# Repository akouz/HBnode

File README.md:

# HBnode
Microcontroller boards for [HBus](https://github.com/akouz/HBus) based on [AVR64DD32](https://www.microchip.com/en-us/product/avr64dd32). Form factor is the same as Arduino Pro Mini and Arduino Nano, while pinout made as close as possible. Firmware update made using on-board I2C EEPROM; custom bootloader occupies 1K bytes. 

[Programmer HEXloader.exe](https://github.com/akouz/HBnode/tree/main/AVR64DD32/Programmer/Software) can transfer compiled hex files from PC to EEPROM via Arduino UNO running [sketch HEXloader.ino](https://github.com/akouz/HBnode/tree/main/AVR64DD32/Programmer/Sketch). When a board used in HBus network, firmware can be updated remotely via HBus.

# How to program HBnode board:
1. Burn bootloader. 
   Plug PicKit4 to 4-pin connector, apply power to the board and burn [HBnode bootloader](https://github.com/akouz/HBnode/blob/main/AVR64DD32/Bootloader) using MPLAB.X IDE or MPLAB.X IPE.

2. Load HBus sketch.
   Connect HBnode to the [programmer](https://github.com/akouz/HBnode/tree/main/AVR64DD32/Programmer) and transfer selected sketch to the HBnode using [HEXLoader](https://github.com/akouz/HBnode/tree/main/AVR64DD32/Programmer/Software)
   
3. When a correct sketch is programmed to the HBnode, a new sketch can be loaded to the board via HBus using [NodeTest](https://github.com/akouz/HBus/tree/master/NodeTest)

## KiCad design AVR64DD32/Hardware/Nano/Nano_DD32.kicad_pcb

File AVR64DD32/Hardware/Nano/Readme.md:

Connector P4 for UPDI programmer/debugger. To program bootloader I used MPLAB X rev 6.05 and PicKit4.

Connector P3 for a I2C programmer or for external monitor based on FT200XD. [I2C programmer](https://github.com/akouz/HBnode/tree/main/AVR64DD32/Programmer) writes application code into serial EEPROM U1, after reset bootloader copies EEPROM into program memory. Arduino UNO can be used as [I2C programmer](https://github.com/akouz/HBnode/tree/main/AVR64DD32/Programmer).

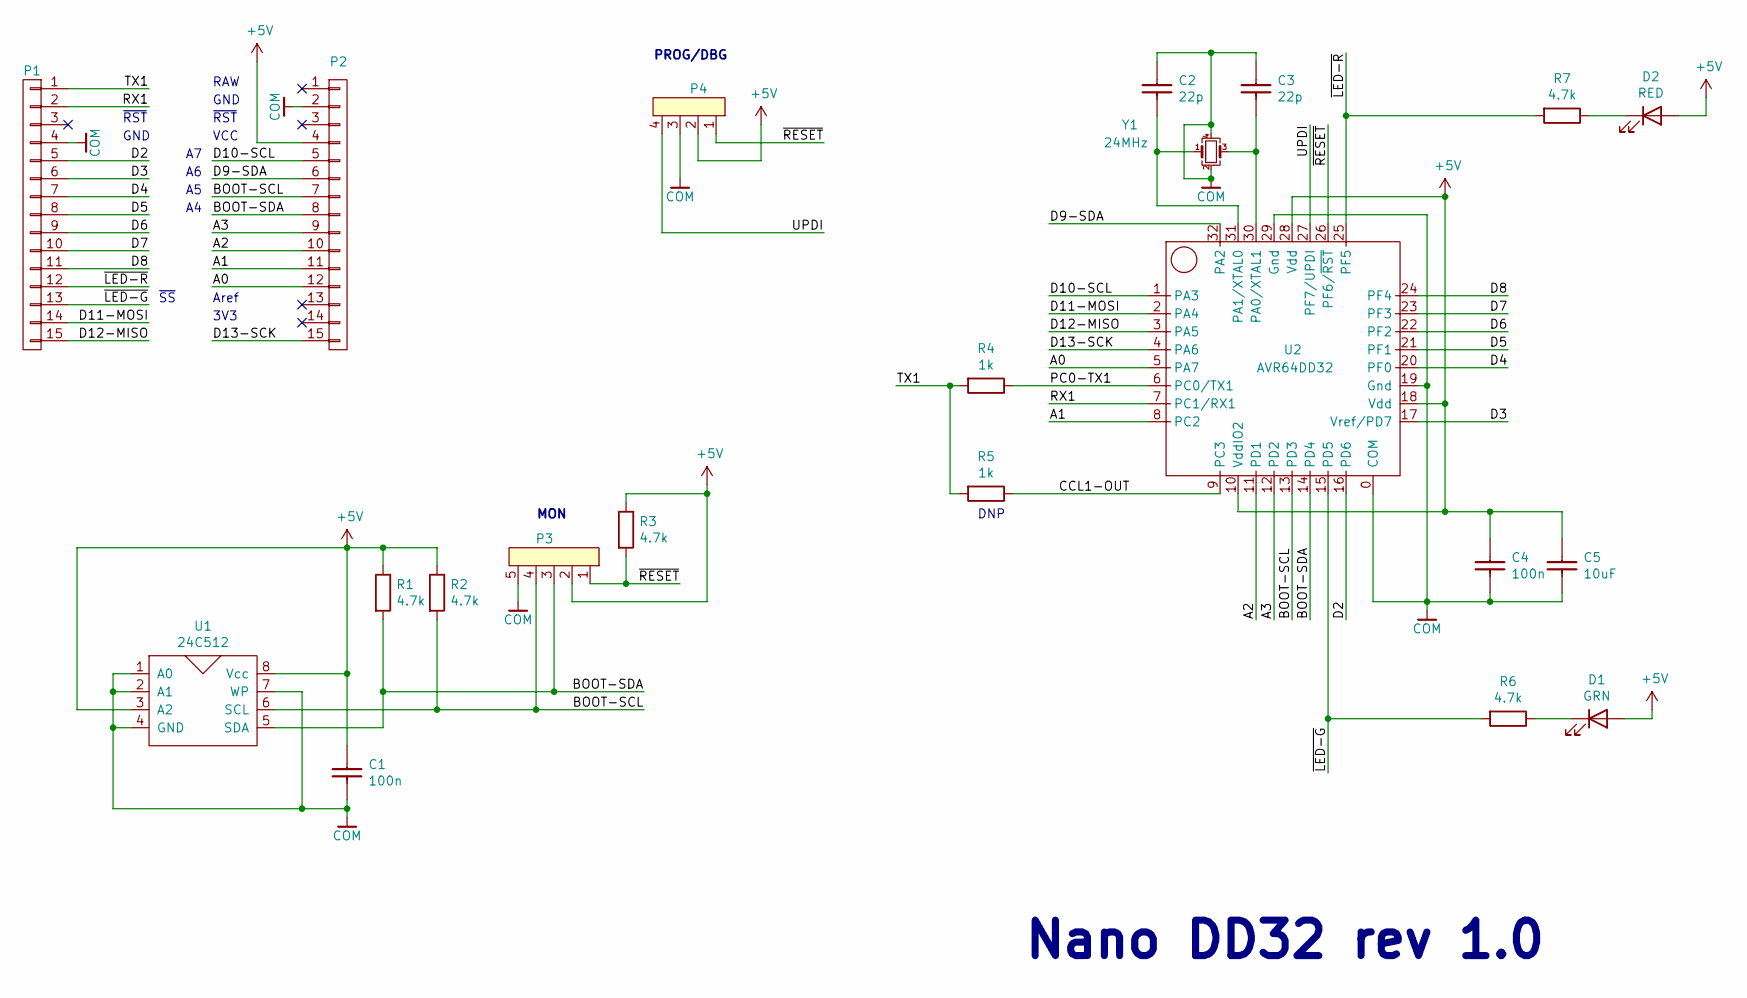
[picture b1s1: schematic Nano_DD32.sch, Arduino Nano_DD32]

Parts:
C1, C4: 100n; 0603
C2, C3: 22p; 0603
C5: 10uF; 0805
D1: GRN; 0603_LED
D2: RED; 0603_LED
P1, P2: CONN_01X15; PinHeader_1x15_P2.54mm_Vertical
P3: CONN_01X05
P4: CONN_01X04; PinHeader_1x04_P2.54mm_Vertical
R1, R2, R3, R6, R7: 4.7k; 0603
R4, R5: 1k; 0603
U1: 24C512; TSSOP-8_4.4x3mm_P0.65mm
U2: AVR64DD32; QFN-32-1EP_5x5mm_P0.5mm_EP3.1x3.1mm_pin0
Y1: 24MHz; Crystal_SMD_2520-4Pin_2.5x2.0mm

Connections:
+5V: C1.1, C4.1, C5.1, D1.2 (A), D2.2 (A), P2.4, P3.2, P4.2, R1.1, R2.1, R3.1, U1.3 (A2), U1.8 (Vcc), U2.10 (VddIO2), U2.18 (Vdd), U2.28 (Vdd)
/A0: P2.12, U2.5 (PA7)
/A1: P2.11, U2.8 (PC2)
/A2: P2.10, U2.11 (PD1)
/A3: P2.9, U2.12 (PD2)
/BOOT-SCL: P2.7, P3.4, R2.2, U1.6 (SCL), U2.13 (PD3)
/BOOT-SDA: P2.8, P3.3, R1.2, U1.5 (SDA), U2.14 (PD4)
/CCL1-OUT: R5.1, U2.9 (PC3)
/D2: P1.5, U2.16 (PD6)
/D3: P1.6, U2.17 (Vref/PD7)
/D4: P1.7, U2.20 (PF0)
/D5: P1.8, U2.21 (PF1)
/D6: P1.9, U2.22 (PF2)
/D7: P1.10, U2.23 (PF3)
/D8: P1.11, U2.24 (PF4)
/D9-SDA: P2.6, U2.32 (PA2)
/D10-SCL: P2.5, U2.1 (PA3)
/D11-MOSI: P1.14, U2.2 (PA4)
/D12-MISO: P1.15, U2.3 (PA5)
/D13-SCK: P2.15, U2.4 (PA6)
/PC0-TX1: R4.1, U2.6 (PC0/TX1)
/RX1: P1.2, U2.7 (PC1/RX1)
/TX1: P1.1, R4.2, R5.2
/UPDI: P4.4, U2.27 (PF7/UPDI)
/~LED-G: P1.13, R6.2, U2.15 (PD5)
/~LED-R: P1.12, R7.2, U2.25 (PF5)
/~RESET: P3.1, P4.1, R3.2, U2.26 (PF6/~RST)
COM: C1.2, C2.1, C3.1, C4.2, C5.2, P1.4, P2.2, P3.5, P4.3, U1.1 (A0), U1.2 (A1), U1.4 (GND), U1.7 (WP), U2.0 (COM), U2.19 (Gnd), U2.29 (Gnd), Y1.2, Y1.4
unnamed: C2.2, U2.31 (PA1/XTAL0), Y1.1
unnamed: C3.2, U2.30 (PA0/XTAL1), Y1.3
unnamed: D1.1 (K), R6.1
unnamed: D2.1 (K), R7.1

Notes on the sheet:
~RST
RAW
GND
VCC
PROG/DBG
MON
~SS
Nano DD32 rev 1.0
Aref
3V3
DNP

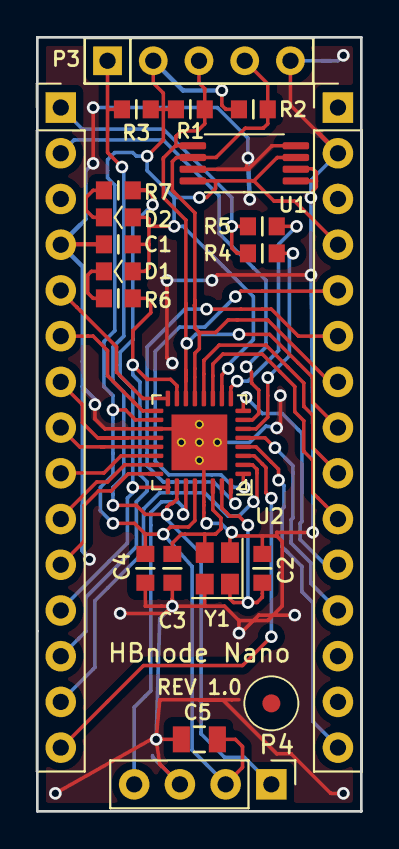
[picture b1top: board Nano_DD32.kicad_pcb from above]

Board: 2 copper layers, 18.0 x 43.0 mm, 22 parts (0 on the bottom side), 32 nets.

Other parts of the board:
FID1: FIDUCIAL; Fiducial

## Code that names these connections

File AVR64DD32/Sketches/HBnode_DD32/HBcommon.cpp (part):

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// =============================================
void EVSYS_config(void)
{
    EVSYS.CHANNEL2 = 0x4E;          // channel 2 source is PD6, it is connected to 
                                    // PC1 (USART1 RxD) by h/w link
    EVSYS.USERCCLLUT2A = 0x03;      // CCL LUT2 event A connected to channel 2
    //EVSYS.USEREVSYSEVOUTA = 0x03;   // EVSYS EVOUTA pin PA2 (D9) connected to channel 2, debug
}
// =============================================
// Configure CCL
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    CCL.LUT0CTRLB = 0x00;   
    CCL.LUT0CTRLC = 0x08;   // INSEL2 to USART1 TxD    
    CCL.TRUTH0    = 0xF0;      
    // CCL.LUT0CTRLA = 0x41;   // OUTEN to PA3,  debug 

    // -----------
    // LUT1 - combines D flip-flop output and USART1 TxD
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    CCL.LUT1CTRLB = 0x02;   // INSEL0 to LUT2 output, eg to D flip-flop output
    CCL.LUT1CTRLC = 0x08;   // INSEL2 to USART1 TxD   
    CCL.TRUTH1    = 0xFA;   // when D flip-flop is set then output is high, eg recessive state on HBus
    CCL.LUT1CTRLA = 0x61;   // OUTEN to PC3, filter, clock CLK_PER 

    // -----------
    // LUT2 - D input of flip-flop and flip-flop output
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
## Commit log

2023-04-25 Create AVR64DD32
2023-08-20 Add files via upload
    rev 1.8
2023-08-21 Add files via upload
    rev 1.9
2023-09-13 Add files via upload
    preliminary rev 0.9
2023-10-19 Add files via upload
    rev 1.1
2023-10-19 Add files via upload
    rev 0.14

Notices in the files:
AVR64DD32/Sketches/HBnode_DD32/HBcommon.cpp:
(c) 2023 Alex Kouznetsov,  https://github.com/akouz/hbus
